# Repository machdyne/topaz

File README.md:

# Topaz Computer

Topaz is a headless computer that uses an ASIC module based on the open-source [KIAN-V RV32 SOC](https://github.com/splinedrive/gf180mcu-kianv-rv32ima-sv32).

This repo contains schematics, PCB layouts, firmware and documentation.

Find more information on the [Topaz product page](https://machdyne.com/product/topaz-computer/).

## License

The contents of this repo are released under the [Lone Dynamics Open License](LICENSE.md) with the following exceptions:

  * The ch32fun library is MIT licensed.

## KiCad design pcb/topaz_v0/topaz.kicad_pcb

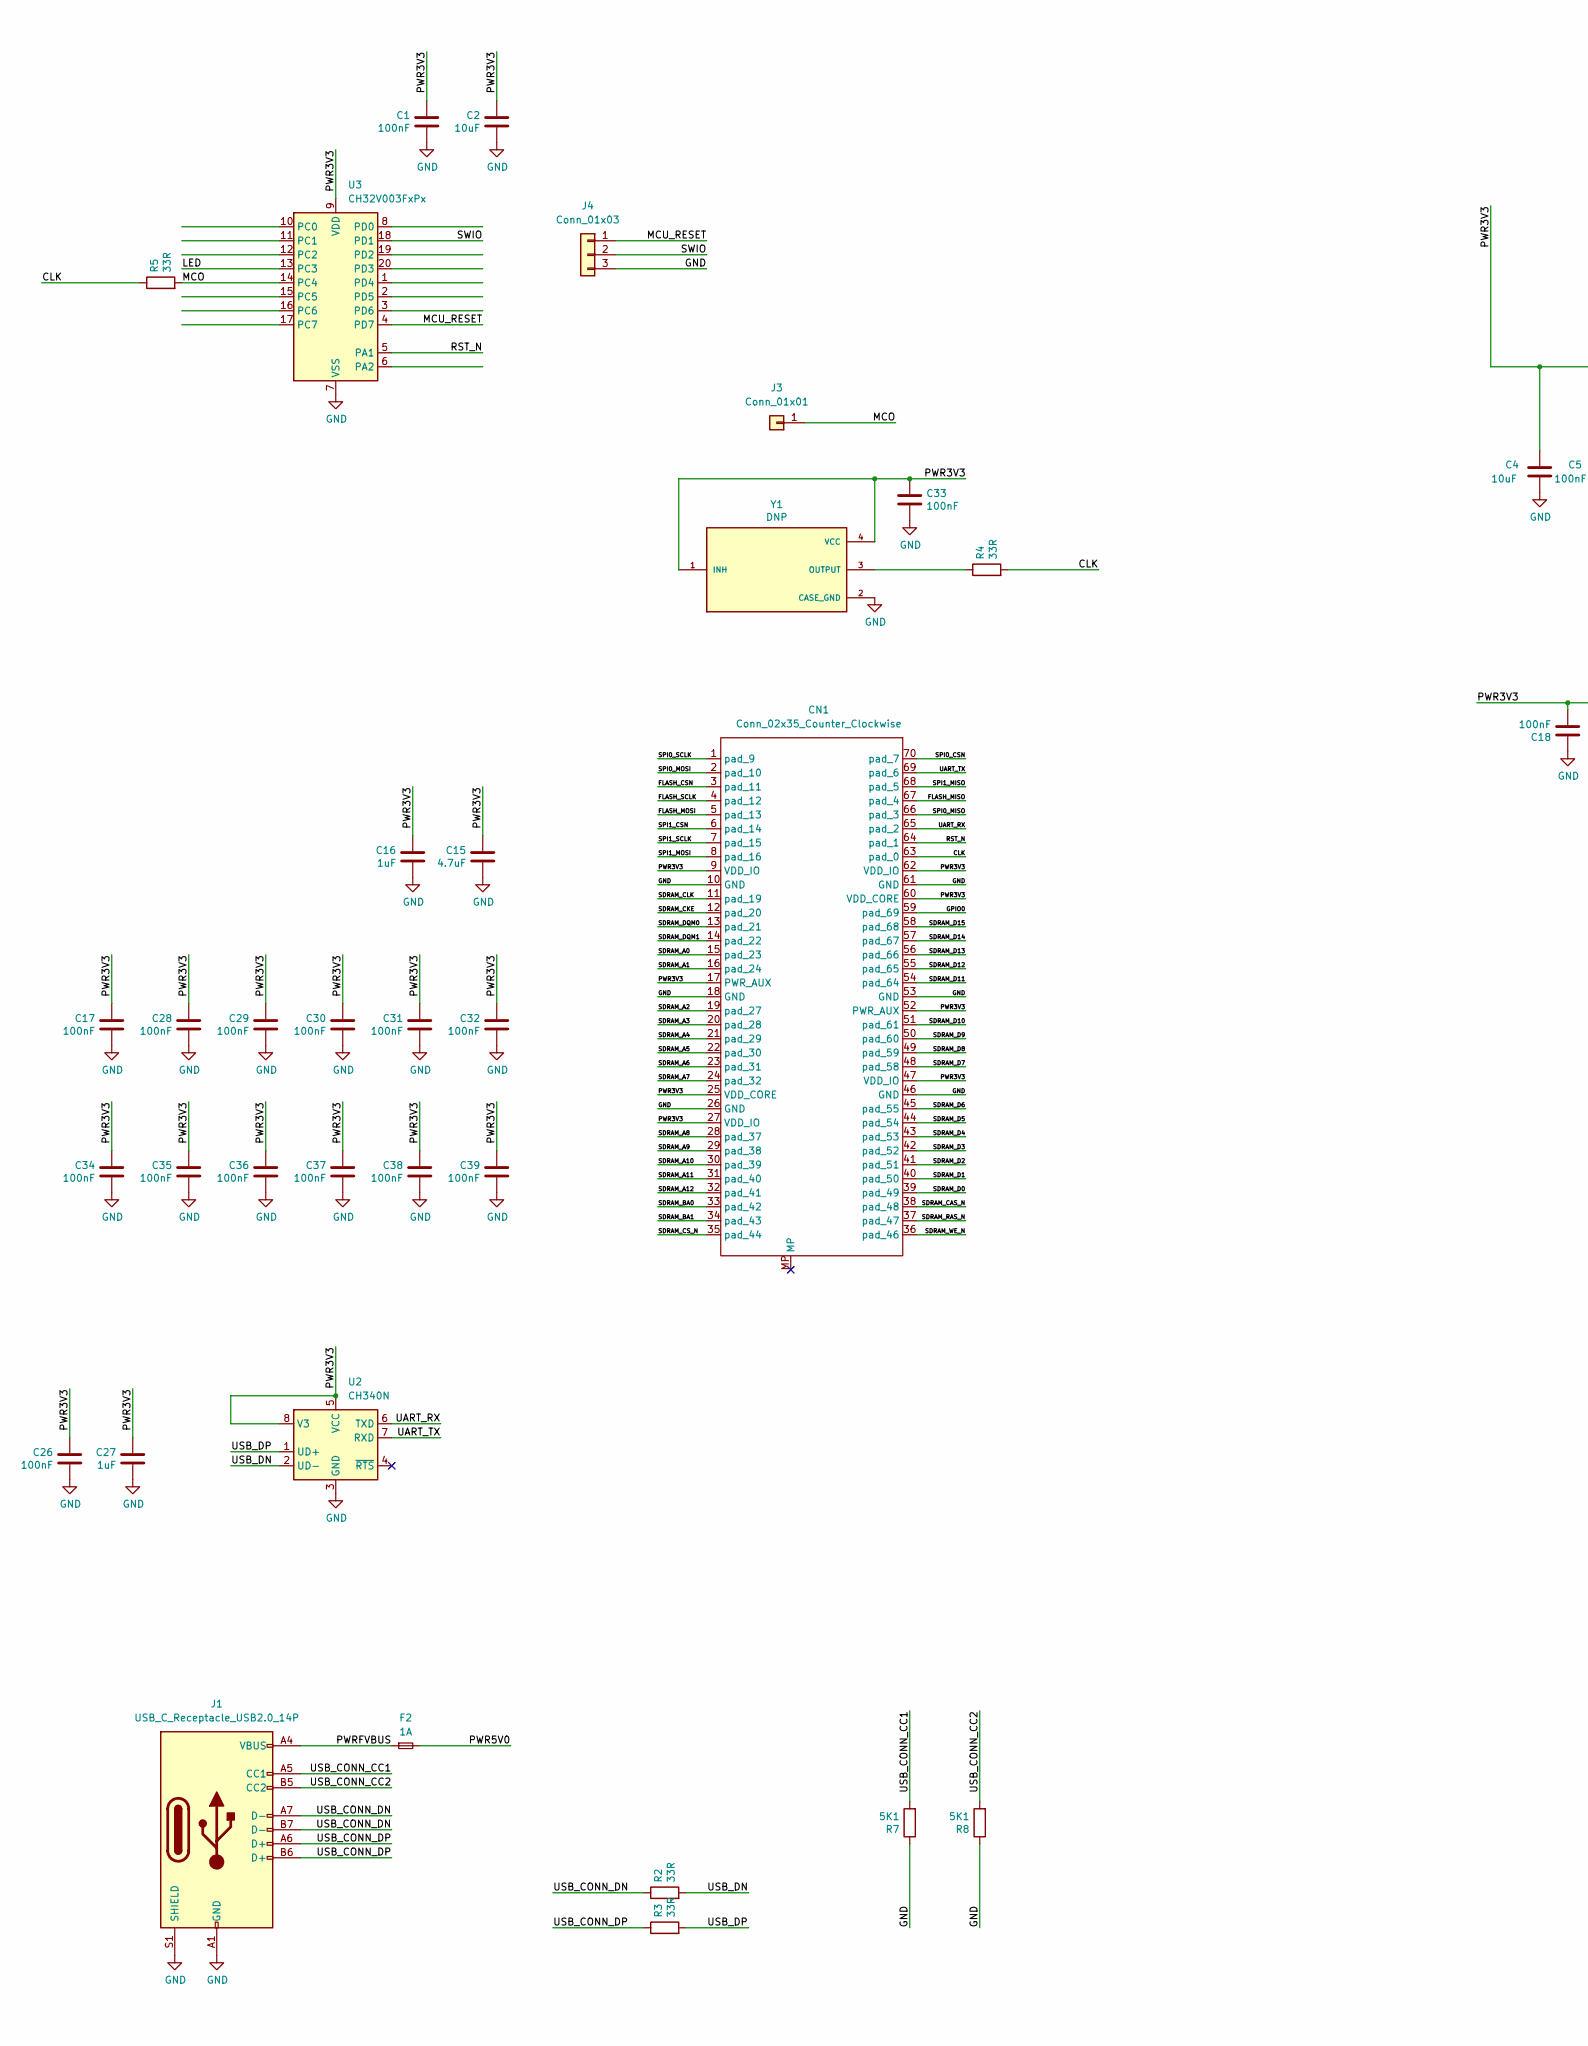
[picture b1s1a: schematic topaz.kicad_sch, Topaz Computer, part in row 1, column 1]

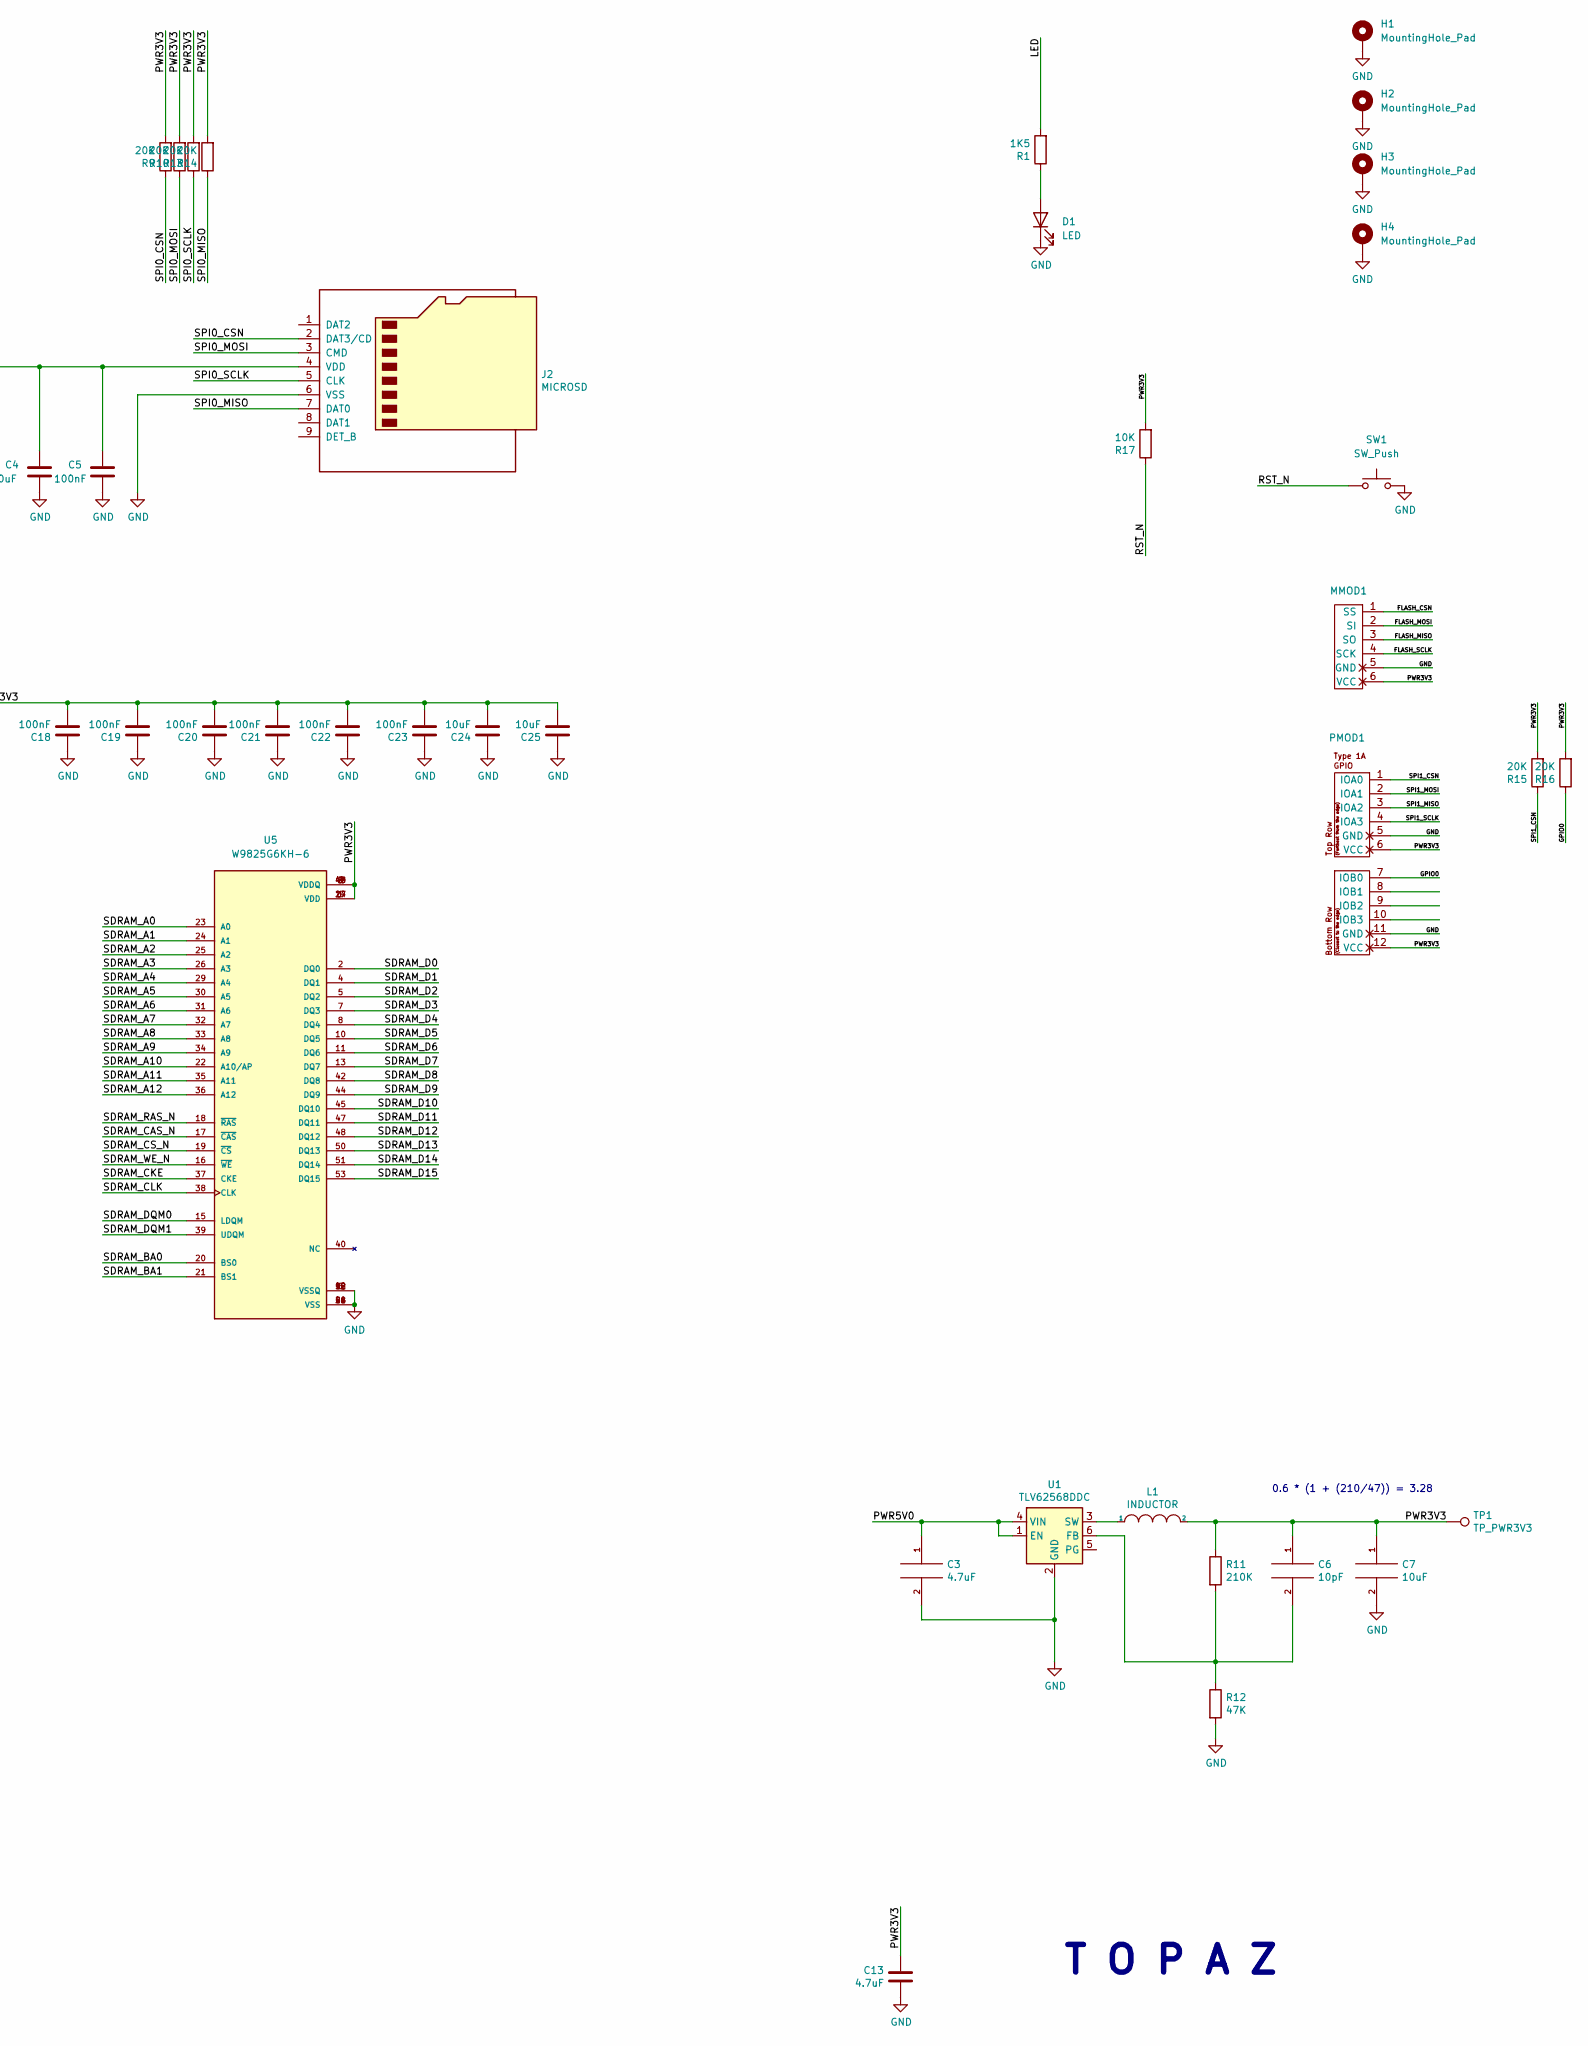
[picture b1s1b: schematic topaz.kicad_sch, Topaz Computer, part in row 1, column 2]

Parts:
C1, C5, C18, C19, C20, C21, C22, C23, C26: 100nF; C_0603_1608Metric
C2, C4, C7, C24, C25: 10uF; C_0603_1608Metric
C3, C13: 4.7uF; C_0603_1608Metric
C6: 10pF; C_0603_1608Metric
C15: 4.7uF; C_0402_1005Metric
C16: 1uF; C_0402_1005Metric
C17, C28, C29, C30, C31, C32, C34, C35, C36, C37, C38, C39: 100nF; C_0402_1005Metric
C27: 1uF; C_0603_1608Metric
C33: 100nF; R_0603_1608Metric
CN1: Conn_02x35_Counter_Clockwise; CONN-SMD_70P-P0.40_HC-PBB40C-70DS-0.4V-3.0-02
D1: LED; LED_1206_3216Metric
F2: 1A; Fuse_0805_2012Metric
H1, H2, H3, H4: MountingHole_Pad; MountingHole_2.7mm_M2.5_DIN965_Pad
J1: USB_C_Receptacle_USB2.0_14P; USB_C_Receptacle_HRO_TYPE-C-31-M-12-BIG-PADS-PASTE
J2: MICROSD; TF-018B-H15-HAND-SOLDER
J3: Conn_01x01; PinHeader_1x01_P2.54mm_Vertical
J4: Conn_01x03; PinHeader_1x03_P2.54mm_Vertical
L1: INDUCTOR; L_0805_2012Metric
MMOD1: MMOD_Host_Socket
PMOD1: PMOD-Device-x2-Type-1A-GPIO; PMOD_2x06_HOST
R1: 1K5; R_0603_1608Metric
R2, R3, R4, R5: 33R; R_0402_1005Metric
R7, R8: 5K1; R_0603_1608Metric
R9, R10, R13, R14, R15, R16: 20K; R_0603_1608Metric
R11: 210K; R_0603_1608Metric
R12: 47K; R_0603_1608Metric
R17: 10K; R_0603_1608Metric
SW1: SW_Push; Button_2P_3x4mm
TP1: TP_PWR3V3; TestPoint_THTPad_D1.0mm_Drill0.5mm
U1: TLV62568DDC; SOT-23-6
U2: CH340N; SOP-8_3.9x4.9mm_P1.27mm
U3: CH32V003FxPx; TSSOP-20_4.4x6.5mm_P0.65mm
U5: W9825G6KH-6; SOP80P1176X120-54N; PARTREV A05
Y1: DNP; OSC_KC2016Z13.5600C1KX00; PARTREV November 2020

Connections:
/CLK: CN1.63 (pad_0), R4.2, R5.1
/FLASH_CSN: CN1.3 (pad_11), MMOD1.1 (SS)
/FLASH_MISO: CN1.67 (pad_4), MMOD1.3 (SO)
/FLASH_MOSI: CN1.5 (pad_13), MMOD1.2 (SI)
/FLASH_SCLK: CN1.4 (pad_12), MMOD1.4 (SCK)
/GPIO0: CN1.59 (pad_69), PMOD1.7 (IOB0), R16.1
/LED: R1.2, U3.13 (PC3)
/MCO: J3.1 (Pin_1_1), R5.2, U3.14 (PC4)
/MCU_RESET: J4.1, U3.4 (PD7)
/PWR3V3: C1.1, C2.1, C4.1, C5.1, C6.1, C7.1, C13.1, C15.1, C16.1, C17.1, C18.2, C19.2, C20.2, C21.2, C22.2, C23.2, C24.2, C25.2, C26.1, C27.1, C28.1, C29.1, C30.1, C31.1, C32.1, C33.1, C34.1, C35.1, C36.1, C37.1, C38.1, C39.1, CN1.9 (VDD_IO), CN1.17 (PWR_AUX), CN1.25 (VDD_CORE), CN1.27 (VDD_IO), CN1.47 (VDD_IO), CN1.52 (PWR_AUX), CN1.60 (VDD_CORE), CN1.62 (VDD_IO), J2.4 (VDD), L1.2, MMOD1.6 (VCC), PMOD1.6 (VCC), PMOD1.12 (VCC), R9.2, R10.2, R11.1, R13.2, R14.2, R15.2, R16.2, R17.2, TP1.1 (1_1), U2.5 (VCC), U2.8 (V3), U3.9 (VDD), U5.1 (VDD), U5.3 (VDDQ), U5.9 (VDDQ), U5.14 (VDD), U5.27 (VDD), U5.43 (VDDQ), U5.49 (VDDQ), Y1.1 (INH), Y1.4 (VCC)
/PWR5V0: C3.1, F2.2, U1.1 (EN), U1.4 (VIN)
/PWRFVBUS: F2.1, J1.A4 (VBUS), J1.A9 (VBUS), J1.B4 (VBUS), J1.B9 (VBUS)
/RST_N: CN1.64 (pad_1), R17.1, SW1.1, U3.5 (PA1)
/SDRAM_A0: CN1.15 (pad_23), U5.23 (A0)
/SDRAM_A1: CN1.16 (pad_24), U5.24 (A1)
/SDRAM_A2: CN1.19 (pad_27), U5.25 (A2)
/SDRAM_A3: CN1.20 (pad_28), U5.26 (A3)
/SDRAM_A4: CN1.21 (pad_29), U5.29 (A4)
/SDRAM_A5: CN1.22 (pad_30), U5.30 (A5)
/SDRAM_A6: CN1.23 (pad_31), U5.31 (A6)
/SDRAM_A7: CN1.24 (pad_32), U5.32 (A7)
/SDRAM_A8: CN1.28 (pad_37), U5.33 (A8)
/SDRAM_A9: CN1.29 (pad_38), U5.34 (A9)
/SDRAM_A10: CN1.30 (pad_39), U5.22 (A10/AP)
/SDRAM_A11: CN1.31 (pad_40), U5.35 (A11)
/SDRAM_A12: CN1.32 (pad_41), U5.36 (A12)
/SDRAM_BA0: CN1.33 (pad_42), U5.20 (BS0)
/SDRAM_BA1: CN1.34 (pad_43), U5.21 (BS1)
/SDRAM_CAS_N: CN1.38 (pad_48), U5.17 (~CAS)
/SDRAM_CKE: CN1.12 (pad_20), U5.37 (CKE)
/SDRAM_CLK: CN1.11 (pad_19), U5.38 (CLK)
/SDRAM_CS_N: CN1.35 (pad_44), U5.19 (~CS)
/SDRAM_D0: CN1.39 (pad_49), U5.2 (DQ0)
/SDRAM_D1: CN1.40 (pad_50), U5.4 (DQ1)
/SDRAM_D2: CN1.41 (pad_51), U5.5 (DQ2)
/SDRAM_D3: CN1.42 (pad_52), U5.7 (DQ3)
/SDRAM_D4: CN1.43 (pad_53), U5.8 (DQ4)
/SDRAM_D5: CN1.44 (pad_54), U5.10 (DQ5)
/SDRAM_D6: CN1.45 (pad_55), U5.11 (DQ6)
/SDRAM_D7: CN1.48 (pad_58), U5.13 (DQ7)
/SDRAM_D8: CN1.49 (pad_59), U5.42 (DQ8)
/SDRAM_D9: CN1.50 (pad_60), U5.44 (DQ9)
/SDRAM_D10: CN1.51 (pad_61), U5.45 (DQ10)
/SDRAM_D11: CN1.54 (pad_64), U5.47 (DQ11)
/SDRAM_D12: CN1.55 (pad_65), U5.48 (DQ12)
/SDRAM_D13: CN1.56 (pad_66), U5.50 (DQ13)
/SDRAM_D14: CN1.57 (pad_67), U5.51 (DQ14)
/SDRAM_D15: CN1.58 (pad_68), U5.53 (DQ15)
/SDRAM_DQM0: CN1.13 (pad_21), U5.15 (LDQM)
/SDRAM_DQM1: CN1.14 (pad_22), U5.39 (UDQM)
/SDRAM_RAS_N: CN1.37 (pad_47), U5.18 (~RAS)
/SDRAM_WE_N: CN1.36 (pad_46), U5.16 (~WE)
/SPI0_CSN: CN1.70 (pad_7), J2.2 (DAT3/CD), R9.1
/SPI0_MISO: CN1.66 (pad_3), J2.7 (DAT0), R14.1
/SPI0_MOSI: CN1.2 (pad_10), J2.3 (CMD), R10.1
/SPI0_SCLK: CN1.1 (pad_9), J2.5 (CLK), R13.1
/SPI1_CSN: CN1.6 (pad_14), PMOD1.1 (IOA0), R15.1
/SPI1_MISO: CN1.68 (pad_5), PMOD1.3 (IOA2)
/SPI1_MOSI: CN1.8 (pad_16), PMOD1.2 (IOA1)
/SPI1_SCLK: CN1.7 (pad_15), PMOD1.4 (IOA3)
/SWIO: J4.2, U3.18 (PD1)
/UART_RX: CN1.65 (pad_2), U2.6 (TXD)
/UART_TX: CN1.69 (pad_6), U2.7 (RXD)
/USB_CONN_CC1: J1.A5 (CC1), R7.2
/USB_CONN_CC2: J1.B5 (CC2), R8.2
/USB_CONN_DN: J1.A7 (D-), J1.B7 (D-), R2.1
/USB_CONN_DP: J1.A6 (D+), J1.B6 (D+), R3.1
/USB_DN: R2.2, U2.2 (UD-)
/USB_DP: R3.2, U2.1 (UD+)
GND: C1.2, C2.2, C3.2, C4.2, C5.2, C7.2, C13.2, C15.2, C16.2, C17.2, C18.1, C19.1, C20.1, C21.1, C22.1, C23.1, C24.1, C25.1, C26.2, C27.2, C28.2, C29.2, C30.2, C31.2, C32.2, C33.2, C34.2, C35.2, C36.2, C37.2, C38.2, C39.2, CN1.10 (GND), CN1.18 (GND), CN1.26 (GND), CN1.46 (GND), CN1.53 (GND), CN1.61 (GND), D1.1 (K), H1.1 (1_1), H2.1 (1_1), H3.1 (1_1), H4.1 (1_1), J1.A1 (GND), J1.A12 (GND), J1.B1 (GND), J1.B12 (GND), J1.S1 (SHIELD), J2.6 (VSS), J4.3, MMOD1.5 (GND), PMOD1.5 (GND), PMOD1.11 (GND), R7.1, R8.1, R12.2, SW1.2, U1.2 (GND), U2.3 (GND), U3.7 (VSS), U5.6 (VSSQ), U5.12 (VSSQ), U5.28 (VSS), U5.41 (VSS), U5.46 (VSSQ), U5.52 (VSSQ), U5.54 (VSS), Y1.2 (CASE_GND)
unnamed: D1.2 (A), R1.1
unnamed: C6.2, R11.2, R12.1, U1.6 (FB)
unnamed: L1.1, U1.3 (SW)
unnamed: R4.1, Y1.3 (OUTPUT)

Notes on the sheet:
T O P A Z
0.6 * (1 + (210/47)) = 3.28

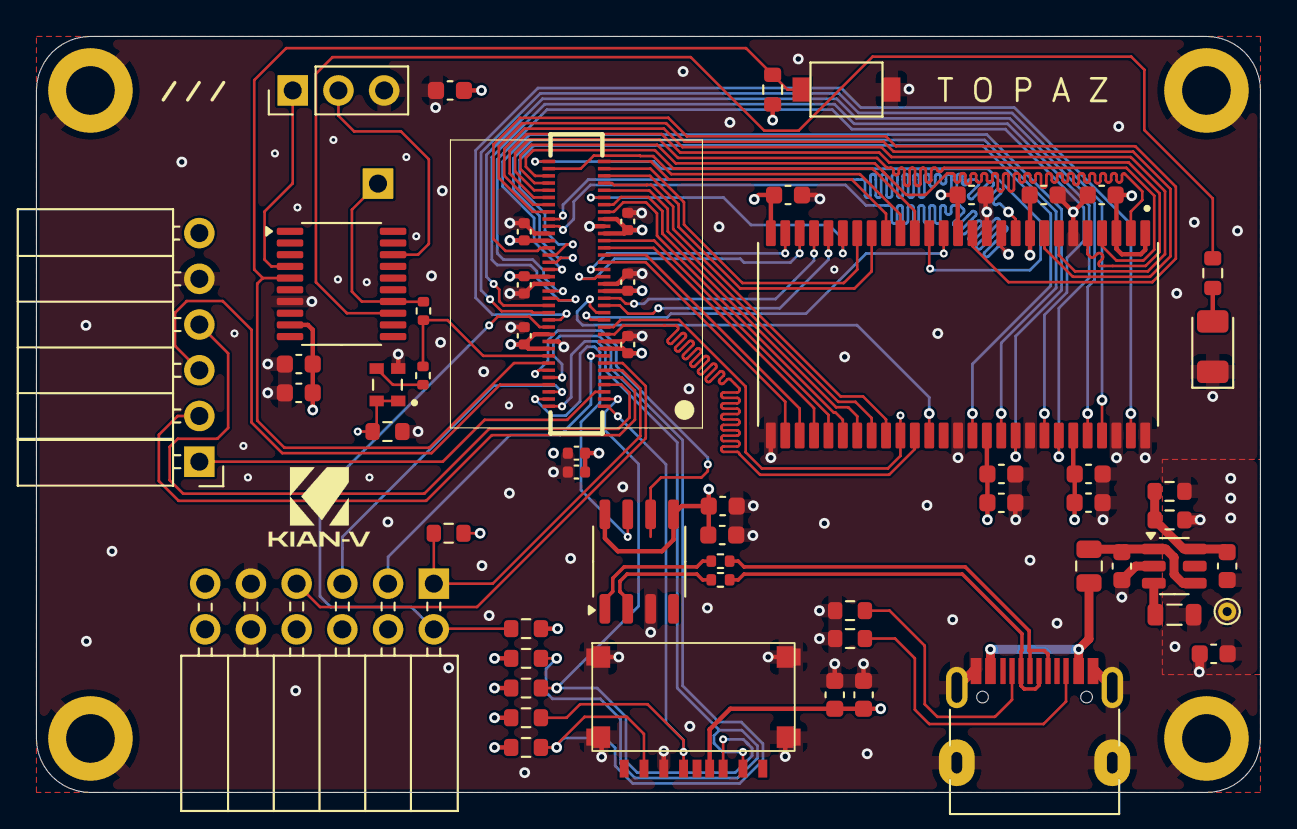
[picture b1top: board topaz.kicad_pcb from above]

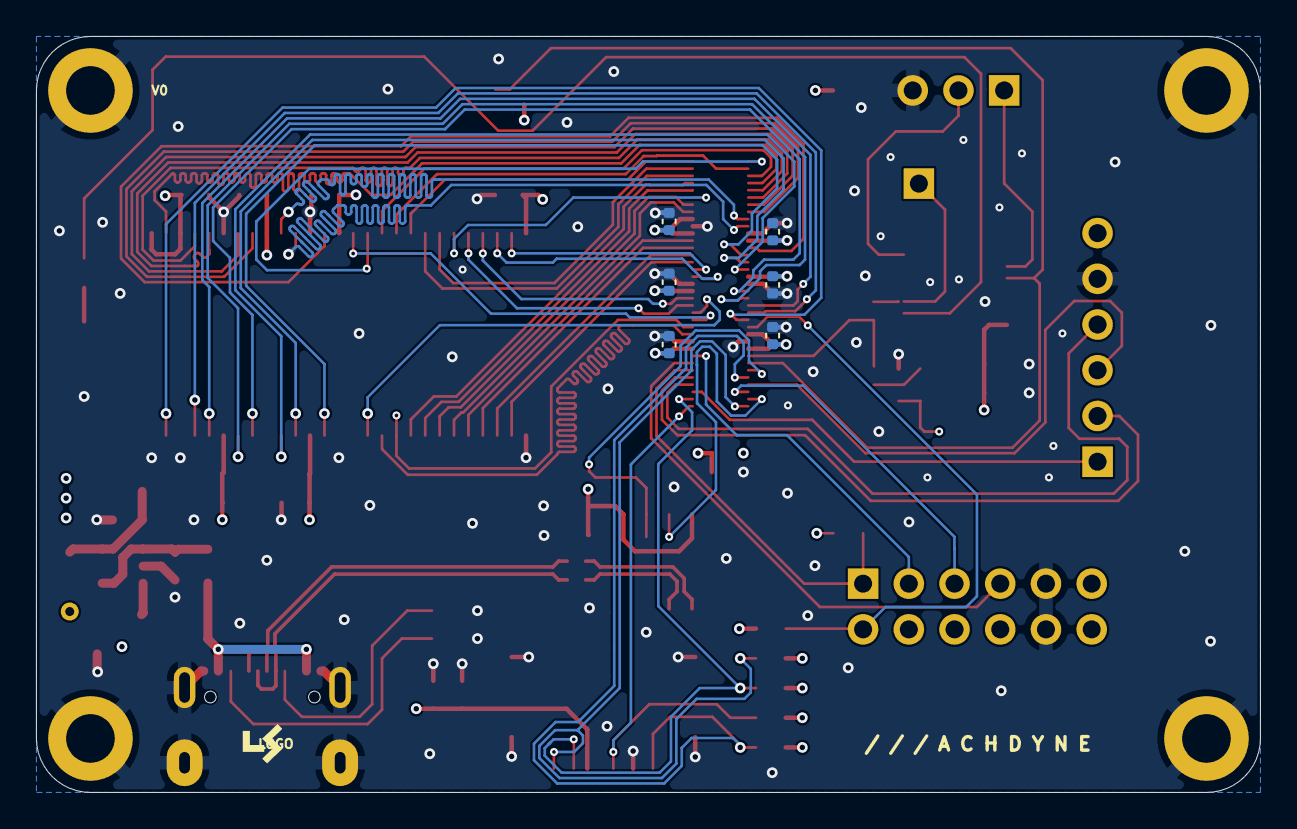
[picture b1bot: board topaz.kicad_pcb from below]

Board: 4 copper layers, 68.0 x 42.0 mm, 70 parts (6 on the bottom side), 74 nets.

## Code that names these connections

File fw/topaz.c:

/*
 * Topaz Firmware
 *
 */

#include <stdio.h>
#include <string.h>
#include <stdint.h>
#include "ch32fun.h"

#define LED_PIN 3   /* PC3 */
#define MCO_PIN 4   /* PC4 */
#define RST_PIN 1   /* PA1 -> ASIC RST_N */

/* Select the MCO output frequency, in Hz. Change this one line.
 *
 *   0         -- PC4 driven high-Z (floating input); use this when an
 *                external clock source is supplied on PC4 instead
 *   24000000  -- native MCO peripheral, source = HSI
 *   48000000  -- native MCO peripheral, source = SYSCLK
 *
 * Only these three values are supported. All of them are a single native
 * MCO register write (or, for 0, just switching PC4 to an input) -- no
 * timer is ever involved, so the output is always a clean edge straight
 * from the MCO hardware, and TIM1 is always free for the LED.
 */
#ifndef MCO_FREQ_HZ
//#define MCO_FREQ_HZ 0
#define MCO_FREQ_HZ 24000000
#endif

/* How long to hold RST_N low before releasing it, after MCO is running */
#define RST_PULSE_MS 100

#if MCO_FREQ_HZ == 0
	#define MCO_MODE_EXTERNAL 1
#elif MCO_FREQ_HZ == 24000000
	#define MCO_MODE_NATIVE_HSI 1
#elif MCO_FREQ_HZ == 48000000
	#define MCO_MODE_NATIVE_SYSCLK 1
#else
	#error "MCO_FREQ_HZ must be 0, 24000000, or 48000000."
#endif

/* ── LED (PC3, TIM1 Channel 3 PWM, "breathing" fade) ──────────────────────
 *
 * PC3 is TIM1_CH3 in the default (no-remap) pin mapping. MCO never uses
 * TIM1 now (only the native SYSCLK/HSI mux, or high-Z), so TIM1 is always
 * free for the LED -- a full 256-step, ~3.9 kHz PWM every time, no
 * shared-timer caveats. Brightness follows volume^2 as volume ramps
 * 0..255..0, matching the eye's roughly power-law brightness perception
 * so the fade looks smooth rather than linear/robotic.
 */

#define LED_PWM_PERIOD 256UL

static void led_pwm_init(void)
{
    RCC->APB2PCENR |= RCC_APB2Periph_GPIOC | RCC_APB2Periph_TIM1;

    /* PC3 as TIM1_CH3 alternate function push-pull (default mapping) */
    GPIOC->CFGLR &= ~(0xFu << (4 * LED_PIN));
    GPIOC->CFGLR |=  (GPIO_CNF_OUT_PP_AF | GPIO_Speed_10MHz) << (4 * LED_PIN);

    /* CH3 output compare: PWM mode 1 (OC3M = 110) -- high while CNT < CCR */
    TIM1->CHCTLR2 &= ~(TIM_OC3M | TIM_CC3S);
    TIM1->CHCTLR2 |=  (TIM_OC3M_2 | TIM_OC3M_1);
    TIM1->CH3CVR   = 0;               /* start fully off */
    TIM1->CCER    |= TIM_CC3E;

    /* PSC=47 -> 48MHz/48 = 1MHz timer clock; ATRLR=255 -> ~3.9kHz PWM */
    TIM1->PSC     = 47;
    TIM1->ATRLR   = LED_PWM_PERIOD - 1;
    TIM1->SWEVGR |= TIM_UG;
    TIM1->CTLR1  |= TIM_CEN;
    TIM1->BDTR   |= TIM_MOE;

    printf("led_pwm_init: PC3=TIM1_CH3, PWM period=%lu counts\n",
           (unsigned long)LED_PWM_PERIOD);
}

/* Advance the breathing animation by one step. Call this periodically
 * (e.g. every ~8ms) from the main loop. */
static void led_breathe_step(void)
{
    static uint16_t volume = 0;
    static int8_t   dir = 1;

    uint32_t duty = ((uint32_t)volume * volume * LED_PWM_PERIOD) / (256UL * 256UL);
    TIM1->CH3CVR = duty;

    if (dir > 0) {
        if (volume >= 255) dir = -1; else volume++;
    } else {
        if (volume == 0)   dir = 1;  else volume--;
    }
}

/* ── ASIC reset (RST_N, PA1, active-low, push-pull) ───────────────────────
 *
 * NOTE: PA1/PA2 default to normal GPIO function (AFIO_PCFR1.PA1PA2_RM = 0
 * on reset), so no remap is needed here. If this board ever grows an HSE
 * crystal on PA1/PA2, that bit would need to stay cleared for this to work.
 */

static inline void rst_assert(void)  { GPIOA->BSHR = (1u << (16 + RST_PIN)); } /* drive low  */
static inline void rst_release(void) { GPIOA->BSHR = (1u << RST_PIN); }        /* drive high */

static void rst_init(void)
{
    RCC->APB2PCENR |= RCC_APB2Periph_GPIOA;

    /* Assert reset before the pin becomes an output, so there's no glitch */
    rst_assert();

    GPIOA->CFGLR &= ~(0xFu << (4 * RST_PIN));
    GPIOA->CFGLR |=  (GPIO_Speed_10MHz | GPIO_CNF_OUT_PP) << (4 * RST_PIN);

    printf("rst_init: GPIOA CFGLR=0x%08lx OUTDR=0x%08lx (RST_N should read 0/low)\n",
           (unsigned long)GPIOA->CFGLR, (unsigned long)GPIOA->OUTDR);
}

/* ── MCO (clock output on PC4) ────────────────────────────────────────────
 *
 * Native MCO peripheral only -- see the MCO_FREQ_HZ block above. Always a
 * single register write (or a GPIO mode change for the high-Z/external
 * case), never a timer.
 */

static void mco_init(void)
{
    RCC->APB2PCENR |= RCC_APB2Periph_GPIOC;

#if defined(MCO_MODE_EXTERNAL)

    /* External clock supplied on PC4 -- put the pin in floating input
     * (genuinely high-Z, no pull resistor) so the MCU doesn't drive it. */
    GPIOC->CFGLR &= ~(0xFu << (4 * MCO_PIN));
    GPIOC->CFGLR |=  (GPIO_CNF_IN_FLOATING) << (4 * MCO_PIN); /* MODE=00 (input) */

    printf("mco_init: MCO_FREQ_HZ=0 -> PC4 set to floating input (high-Z), "
           "expecting an external clock. GPIOC CFGLR=0x%08lx\n",
           (unsigned long)GPIOC->CFGLR);
    return;

#endif

    /* CNF=10 (mux push-pull output), MODE=11 (30 MHz max speed) */
    GPIOC->CFGLR &= ~(0xFu << (4 * MCO_PIN));
    GPIOC->CFGLR |=  (GPIO_CNF_OUT_PP_AF | GPIO_Speed_30MHz) << (4 * MCO_PIN);

#if defined(MCO_MODE_NATIVE_HSI)

    RCC->CFGR0 = (RCC->CFGR0 & ~RCC_CFGR0_MCO) | RCC_CFGR0_MCO_HSI;
    printf("mco_init: native HSI -> PC4, RCC CFGR0=0x%08lx\n", (unsigned long)RCC->CFGR0);

#elif defined(MCO_MODE_NATIVE_SYSCLK)

    RCC->CFGR0 = (RCC->CFGR0 & ~RCC_CFGR0_MCO) | RCC_CFGR0_MCO_SYSCLK;
    printf("mco_init: native SYSCLK -> PC4, RCC CFGR0=0x%08lx\n", (unsigned long)RCC->CFGR0);

#endif
}

/* ── Main ───────────────────────────────────────────────────────────────── */

int main(void)
{
	SystemInit();
	Delay_Ms(1);

	printf("\n--- Topaz boot ---\n");

	rst_init();     /* RST_N already held low from here */

	mco_init();     /* bring up the clock to the ASIC */
	led_pwm_init(); /* LED breathing PWM               */
	Delay_Ms(RST_PULSE_MS);

	rst_release();  /* let the ASIC come out of reset with a clock present */
	printf("rst_release: GPIOA OUTDR=0x%08lx (RST_N should read 1/high)\n",
	       (unsigned long)GPIOA->OUTDR);

	uint32_t heartbeat = 0;
	while (1) {
		led_breathe_step();
		Delay_Ms(8);
		if ((heartbeat % 128) == 0) {
			printf("heartbeat %lu\n", (unsigned long)(heartbeat / 128));
		}
		heartbeat++;
	}

}

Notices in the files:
pcb/topaz_v0/topaz.kicad_sch:
Copyright © 2026 Lone Dynamics Corporation
